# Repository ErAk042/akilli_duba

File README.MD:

# Bu repository'de projemizin ilk versiyonu bulunmaktadır. Son hali için [-dosyalar daha yüklenmedi-]'i ziyaret edin.

# Akıllı Duba

Izmir Fen Lisesi öğrencileri tarafından 2204-A Lise Öğrencileri Araştırma Projeleri Yarışması için tasarlanan ve üretilen, içinde bulunduğu su ortamından
alg miktarı, iletkenlik, bulanıklık ve sıcaklık gibi parametrelerin ölçümünü yaparak bu verileri gsm aracılığı ile bir web veritabanına yükleyen duba.

## Genel Mekanik Yapı

Dubamızın ana gövdesi olarak elektronik sistemlerin içinde durduğu bir adet su geçirmez kutu kullanılmıştır. Fotodiyot ve LEDlerin bulunduğu optik sensör
bloğu kutunun içinde yer almaktadır. Bu seyede karanlık odanın mekanik yapısı daha basite indirgenebilmektedir ve su geçirmezlik açıısndan daha az muhtamel
hata noktası oluşmaktadır. Yapılacak ölçümlerin gün ışığından etkilenmemesi için kutunun içindeki bir servoya mıknatıslar ile bağlanan ve bu servo aracılığıyla döndürülerek örneğin gireceği delikleri açıp kapayan bir alt mekanizma tasarlandı. Bu sayede ölçümlerde gün ışığından gelen gürültü miktarının en aza indirilmesi amaçlanmıştır. 

## Optik ve Analog Kısım

Dubada, sudaki klrofil miktarı ölçümü için bir adet BPW34 fotodiyot kullanılmıştır. Bunun seçilmesinin temel sebeplerinden biri yüksek hassasiyete ve geiş bir ışığa duyarlı alana sahip olmasıdır. Bulanıklık sensöründe ise üstünde kızılötesi filtreleyen reçineden yapılma lens olması ve yüksek hassasiyet sebebiyle SFH 203-FA kullanılmıştır. Bu iki fotodiyodun da çıkışına sinyali yükseltme amaçlı düşük gürültülü sabit kazançlı(24x) ADPD2210 fotodiyot yükseltici entegresi kullanılmıştır. Bu fotodiyotlardan gelen sinyalleri arduinonun okuyabileceği bir dijital veriye çevirmesi için küçük ayak izine sahip ve I2C bus ile kolayca kullanılabilen ADS1115 analogtan dijitale çevirici entegresi kullanılmıştır. Sensörlerin durması gereken pozisyon neeniyle BPW34 ve ona ait yükseltici ayrı bir karta monte edilmiş ve bu kart ana karta bir adet 90° pin header ile bağlanmıştır. Ana kartta ayrıca kızılötesi fotodiyot için bir adet arduinonun dijital pinleri tarafından kontrol edilebilen mosfet ve bir sabit akım kaynağı kullanılmıştır. UV ledler için pilin gerilimi ile ledlerin çalışma gerilimi arasındaki yakınlık sebebiyle sadce arduinonun dijital pinleri ile açıp kapayabilmeyi sağlamak amacıyla bir mosfet konmuştur.

Optik sensörler ve ADC yi içeren kartın şematiği

Optik sensörler ve ADC yi içeren kartın dağılım şeması

Hassas fotodiyot ve yükselticisini içeren kartın dağılım şeması

## İletkenlik Sensörü

Dubamız aynı zamanda suyun iletkenliğini ölçerek alg patlamalarının ana sebeplerden biri olan suya kirletici madde atılmasını tespit edebilmektedir. Bu ölçümü alırken sinyallerin su içinden geçerken ne kadar zayıfladığını ölçerek suyun ne düzeyde iletken olduğunu tespit eder. Bunu yaparken suyyun hidrolizini önlemek amacıyla suyun içinden CD4060 tarafından üretilen bir kare dalga geçirilerek bu durum önlenmektedir. Ardından bu kare dalga opamplar aracılığıyla doğrultularak Arduino tarafından analog olarak okunmaktadır. 

TDS sensör kartının şematiği

TDS sensör kartının dağılım şeması

------------------------------------------------------------------------------------------------------------------------------------------------------------------

# This repository contains the first prototype of our project. For the final version, please visit [-files yet to be uploaded-].

# Smart Buoy

Designed and produced by the students of Izmir Science High School for the 2204-A High School Students Research Projects Competition.
A buoy that measures parameters such as algae amount, conductivity, turbidity and temperature and uploads these data to a web database via gsm.

## General Mechanical Structure

As the main body of our buoy, a waterproof box was used in which the electronic systems are kept. Optical sensor with photodiodes and LEDs
block is located inside the box. This simplifies the mechanical structure of the darkroom and makes it less likely to be non watertight.
by reducing failure points from which water can get in. In order to prevent the measurements from being affected by daylight, a sub-mechanism was designed that is connected to a servo inside the box with magnets which are rotated by this servo to open and close the compartment where the sample will enter from. Whith this mechanism, our goal is to to minimize the amount of noise from daylight during measurements. 

## Optical and Analog Part

On the buoy, a BPW34 photodiode was used to measure the amount of chlorophyll in the water. This was chosen because it has high sensitivity and a large photosensitive area. For the turbidity sensor, SFH 203-FA was used due to its high sensitivity and the fact that it has a lens made out of infrared filtering resin. A low-noise fixed gain (24x) ADPD2210 photodiode amplifier ic was used to amplify the signal at the output of both photodiodes. In order to convert the signals from these photodiodes into digital data which the arduino can read, the ADS1115 analog-to-digital converter integration was used, which has a small footprint and can be easily used with the I2C bus. Due to the position where the sensors should be at, the BPW34 and its amplifier are mounted on a separate board and this board is connected to the main board with a 90° pin header. The main board also has a constant current source for the infrared photodiode and a mosfet which can be controlled by the digital pins of the arduino. For the UV LEDs, due to the proximity between the voltage of the battery and the operating voltage of the LEDs,only a mosfet was placed to enable on/off only with the digital pins of the arduino.

## Conductivity Sensor

Our buoy can also measure the conductivity of the water to detect contaminants in the water, one of the main causes of algae blooms. It does this by measuring how much the signal attenuates as it passes through the water to determine how conductive the water is. This is done by passing a square wave generated by CD4060 through the water to prevent hydrolysis of the water. This square wave is then rectified through opamps and read as analog value by Arduino.

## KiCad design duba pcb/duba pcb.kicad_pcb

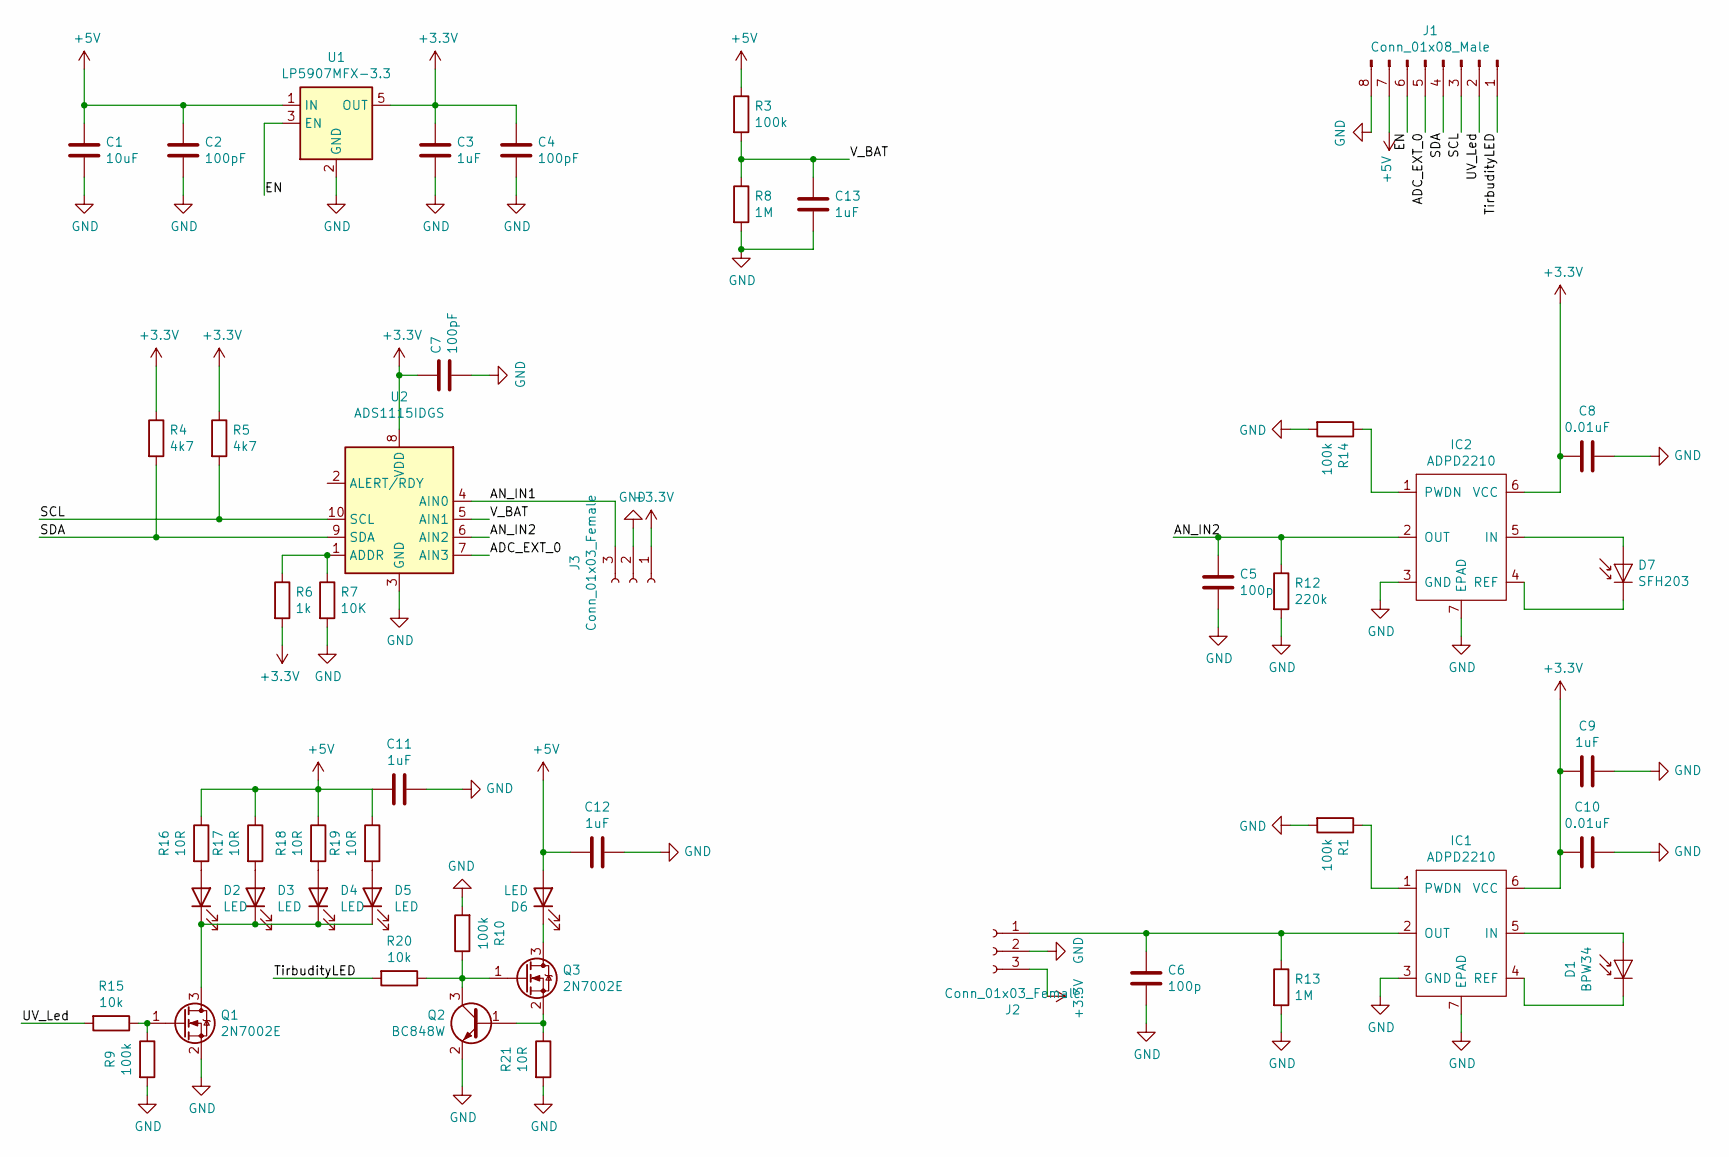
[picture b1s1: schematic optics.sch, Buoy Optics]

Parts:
C1: 10uF; C_0603_1608Metric
C2, C4, C7: 100pF; C_0603_1608Metric
C3, C9, C12, C13: 1uF; C_0603_1608Metric
C5, C6: 100p; C_0603_1608Metric
C8, C10: 0.01uF; C_0603_1608Metric
C11: 1uF; C_0805_2012Metric_Pad1.18x1.45mm_HandSolder
D1: BPW34; BPW34_SMD
D2, D3, D4, D5, D6: LED; LED_D5.0mm
D7: SFH203; LED_D5.0mm_IRGrey
IC1, IC2: ADPD2210; LFCSP-6
J1: Conn_01x08_Male; PinHeader_1x08_P2.54mm_Vertical
J2: Conn_01x03_Female; PinHeader_1x03_P2.54mm_Horizontal
J3: Conn_01x03_Female; PinHeader_1x03_P2.54mm_Vertical
Q1, Q3: 2N7002E; SOT-23
Q2: BC848W; SOT-23
R1, R9, R10, R14: 100k; R_0603_1608Metric
R3: 100k; R_1206_3216Metric
R4, R5: 4k7; R_0603_1608Metric
R6: 1k; R_0603_1608Metric
R7: 10K; R_0603_1608Metric
R8, R13: 1M; R_0603_1608Metric
R12: 220k; R_0603_1608Metric
R15, R20: 10k; R_0603_1608Metric
R16, R17, R18, R19, R21: 10R; R_0603_1608Metric
U1: LP5907MFX-3.3; SOT-23-5
U2: ADS1115IDGS; ADS1115_X2QFN

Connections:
+3V3: C3.1, C4.1, C7.1, C8.2, C9.2, C10.2, IC1.6 (VCC), IC2.6 (VCC), J2.3, J3.1, R4.1, R5.1, R6.2, U1.5 (OUT), U2.8 (VDD)
+5V: C1.1, C2.1, C11.2, C12.2, D6.2 (A), J1.7, R3.1, R16.1, R17.1, R18.1, R19.1, U1.1 (IN)
/optics/ADC_EXT_0: J1.5, U2.7 (AIN3)
/optics/AN_IN1: J3.3, U2.4 (AIN0)
/optics/AN_IN2: C5.1, IC2.2 (OUT), R12.1, U2.6 (AIN2)
/optics/EN: J1.6, U1.3 (EN)
/optics/SCL: J1.3, R5.2, U2.10 (SCL)
/optics/SDA: J1.4, R4.2, U2.9 (SDA)
/optics/TirbudityLED: J1.1, R20.2
/optics/UV_Led: J1.2, R15.2
/optics/V_BAT: C13.1, R3.2, R8.1, U2.5 (AIN1)
GND: C1.2, C2.2, C3.2, C4.2, C5.2, C6.2, C7.2, C8.1, C9.1, C10.1, C11.1, C12.1, C13.2, IC1.3 (GND), IC1.7 (EPAD), IC2.3 (GND), IC2.7 (EPAD), J1.8, J2.2, J3.2, Q1.2 (S), Q2.2 (E), R1.2, R7.2, R8.2, R9.2, R10.2, R12.2, R13.2, R14.2, R21.2, U1.2 (GND), U2.3 (GND)
unnamed: C6.1, IC1.2 (OUT), J2.1, R13.1
unnamed: D1.1 (K), IC1.4 (REF)
unnamed: D1.2 (A), IC1.5 (IN)
unnamed: D2.1 (K), D3.1 (K), D4.1 (K), D5.1 (K), Q1.3 (D)
unnamed: D2.2 (A), R16.2
unnamed: D3.2 (A), R17.2
unnamed: D4.2 (A), R18.2
unnamed: D5.2 (A), R19.2
unnamed: D6.1 (K), Q3.3 (D)
unnamed: D7.1 (K), IC2.4 (REF)
unnamed: D7.2 (A), IC2.5 (IN)
unnamed: IC1.1 (PWDN), R1.1
unnamed: IC2.1 (PWDN), R14.1
unnamed: Q1.1 (G), R9.1, R15.1
unnamed: Q2.1 (B), Q3.2 (S), R21.1
unnamed: Q2.3 (C), Q3.1 (G), R10.1, R20.1
unnamed: R6.1, R7.1, U2.1 (ADDR)

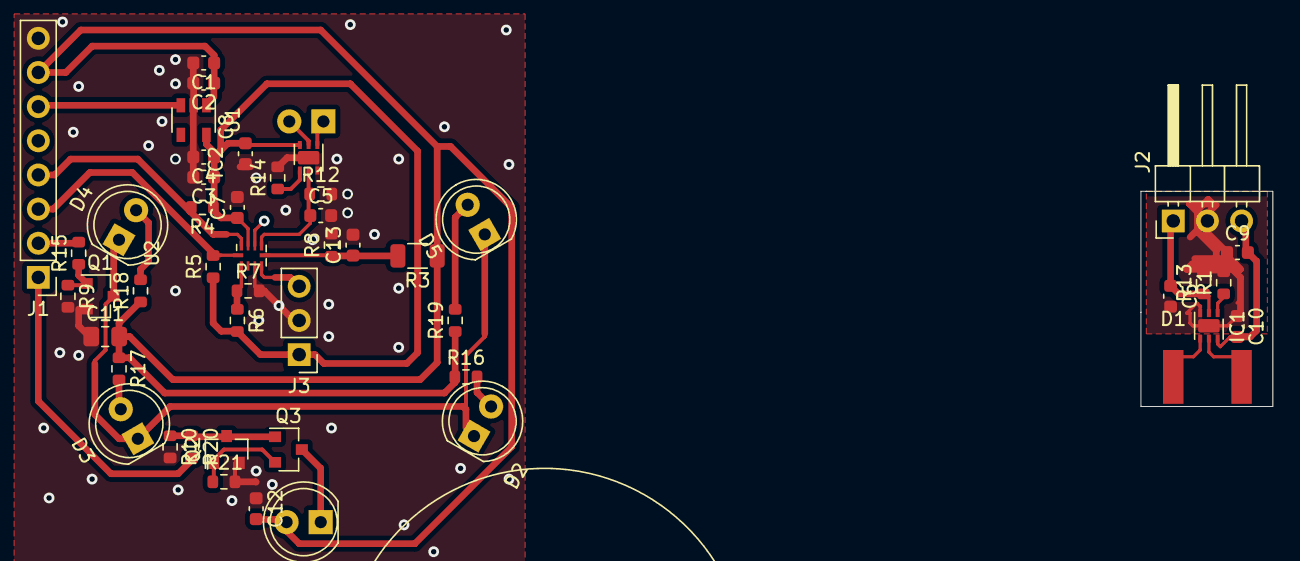
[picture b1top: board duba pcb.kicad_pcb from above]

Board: 2 copper layers, 9.8 x 16.0 mm, 49 parts (1 on the bottom side), 29 nets.

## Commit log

2022-12-29 PCBlerin çizimleri
    Sistemin analog kısmı ve ADS1115 ADC yi içeren kısmı
2022-12-29 Sensör bloğu 3d çizimleri
    LED, fotodiyot ve sensör kartlarının bağlı olduğu plastık parçanın 3B çizimleri. 3B yazıcıdan bastırmaya uygun.
2022-12-30 ADS1115 okuma şu andaki hali
2022-12-30 özel fonksiyon ile daha kolay MUX ve PGA ayarı
2023-01-02 Rename README.md to README.MD
2023-01-02 dubanın ışığı bloke etme mekanizması
2023-01-06 Create resimler
2023-01-06 Update resimler
2023-01-06 Create a
2023-04-04 duba konu (en)
2023-04-13 Rename duba 2 v2.step to sensor_blok
2023-04-13 Rename olcum1.ino to seri_port_debug.ino
2023-06-02 Update sensor_blok
